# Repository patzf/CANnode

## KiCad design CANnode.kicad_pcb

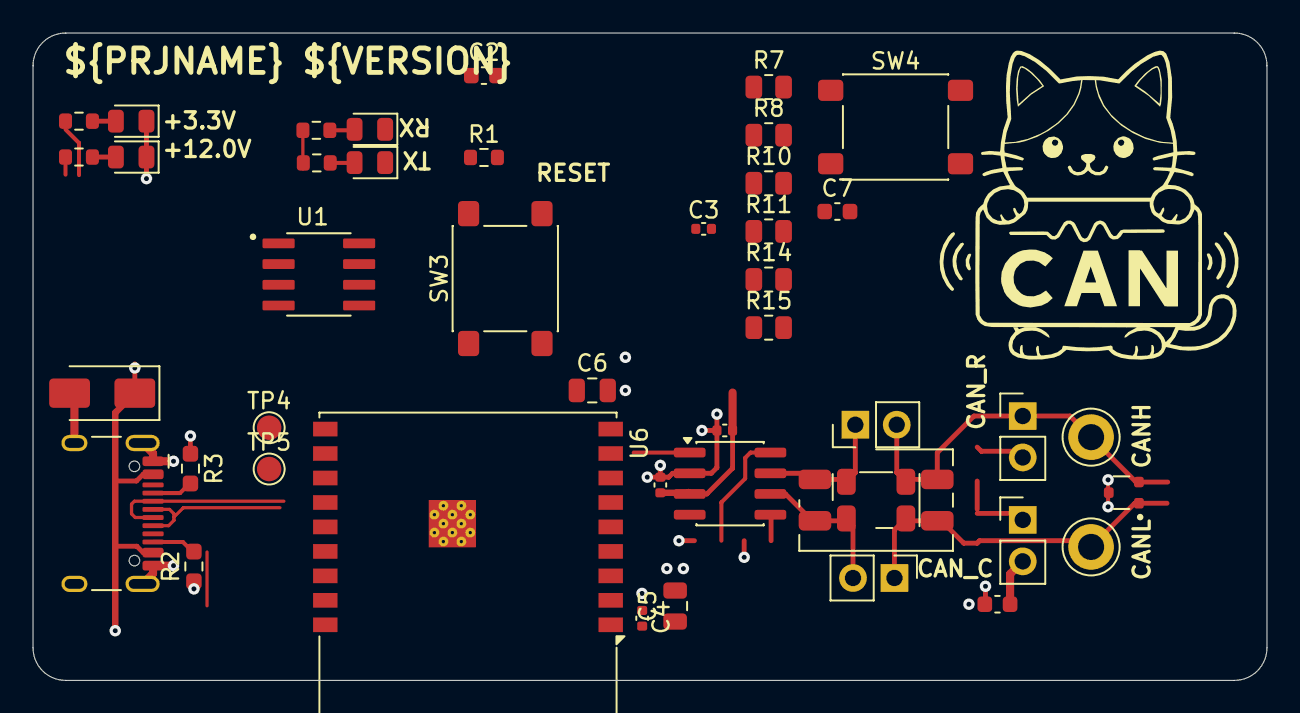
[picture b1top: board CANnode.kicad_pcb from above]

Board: 2 copper layers, 75.7 x 39.7 mm, 44 parts (0 on the bottom side), 27 nets.

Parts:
C2, C7: 100nF; C_0603_1608Metric
C3, C4, C19, C21: 100n; C_0402_1005Metric
C5, C6: 10µF; C_0805_2012Metric
C20: 4.7nF; C_0603_1608Metric
D2, D6: KT-0805G; LED_0805_2012Metric
D3, D8: KT-0805Y; LED_0805_2012Metric
D7: SMAJ5.0A; D_SMA
D13: PESD2CANFD24V-UX; TVS_PESD2CANFD24V-UX
J1: USB_C_Receptacle_USB2.0_16P; USB_C_Receptacle_HCTL_HC-TYPE-C-16P-01A
JP2, JP4, JP7, JP8: Jumper_2_Open; PinHeader_1x02_P2.54mm_Vertical
L2: 1000 uH; L_Wurth_WE-SL2-74422x
L4: 100 uH; L_Wurth_WE-CNSW-1812
R1: 10k; R_0603_1608Metric
R2, R3: 5.1k; R_0603_1608Metric_Pad0.98x0.95mm_HandSolder
R5, R9, R12, R13: 2.2k; R_0603_1608Metric
R7, R8: 0R; R_0805_2012Metric
R10, R11, R14, R15: 120; R_0805_2012Metric
SW3, SW4: SW_Push; SW_SPST_PTS645Sx43SMTR92
TP2, TP3: TestPoint; TP_Keystone_5010-5014_Multipurpose
TP4, TP5: TestPoint_Alt; TestPoint_Pad_D1.5mm
U1: TPS54331DR; SOIC127P599X175-8N
U3: TCAN3413DR; SOIC-8_3.9x4.9mm_P1.27mm
U6: ESP32-C3-WROOM-02-N4; ESP32-C3-WROOM-02

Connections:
+3.3V: C7.2, C19.2, C21.2, R5.2, R7.1, R12.2, R13.2, U3.3 (VCC)
+3V3: C4.2, C5.1, C6.1, R1.1, U6.1 (3V3)
/CAN_RXD: U3.4 (RXD), U6.3 (IO4)
/CAN_STB: R8.1, U3.8 (S)
/CAN_TXD: U3.1 (TXD), U6.4 (IO5)
/CH340_RXD: TP5.1 (1_1), U6.12 (IO21/TXD)
/CH340_TXD: TP4.1 (1_1), U6.11 (IO20/RXD)
/GPIO_START: C3.2, SW3.2
/RESET: C2.2, R1.2, SW4.2, U6.2 (EN)
/USB_D+: J1.A6 (D+), J1.B6 (D+), U6.14 (IO19)
/USB_D-: J1.A7 (D-), J1.B7 (D-), U6.13 (IO18)
GND: C2.1, C3.1, C4.1, C5.2, C6.2, C7.1, C19.1, C20.1, C21.1, D2.1 (K), D3.1 (K), D7.A, D13.3, J1.A1 (GND), J1.A12 (GND), J1.B1 (GND), J1.B12 (GND), J1.S1 (SHIELD), R2.1, R3.1, R8.2, SW3.1, SW4.1, U3.2 (GND), U6.9 (GND), U6.19 (GND)
unnamed: D2.2 (A), R5.1
unnamed: D3.2 (A), R9.1
unnamed: D6.2 (A), R12.1
unnamed: D8.2 (A), R13.1
unnamed: J1.A5 (CC1), R3.2
unnamed: J1.B5 (CC2), R2.2
unnamed: D13.2, JP2.1 (A), JP7.2 (B), L2.4, L4.3, TP2.1 (1_1)
unnamed: JP2.2 (B), R10.1, R14.1
unnamed: JP4.1 (A), R10.2, R11.1, R14.2, R15.1
unnamed: C20.2, JP4.2 (B)
unnamed: JP7.1 (A), L2.1, L4.4, U3.7 (CANH)
unnamed: D13.1, JP8.1 (A), L2.3, L4.2, R11.2, R15.2, TP3.1 (1_1)
unnamed: JP8.2 (B), L2.2, L4.1, U3.6 (CANL)
unnamed: R7.2, U3.5 (SHDN)
VBUS: D7.C, J1.A4 (VBUS), J1.A9 (VBUS), J1.B4 (VBUS), J1.B9 (VBUS), R9.2
